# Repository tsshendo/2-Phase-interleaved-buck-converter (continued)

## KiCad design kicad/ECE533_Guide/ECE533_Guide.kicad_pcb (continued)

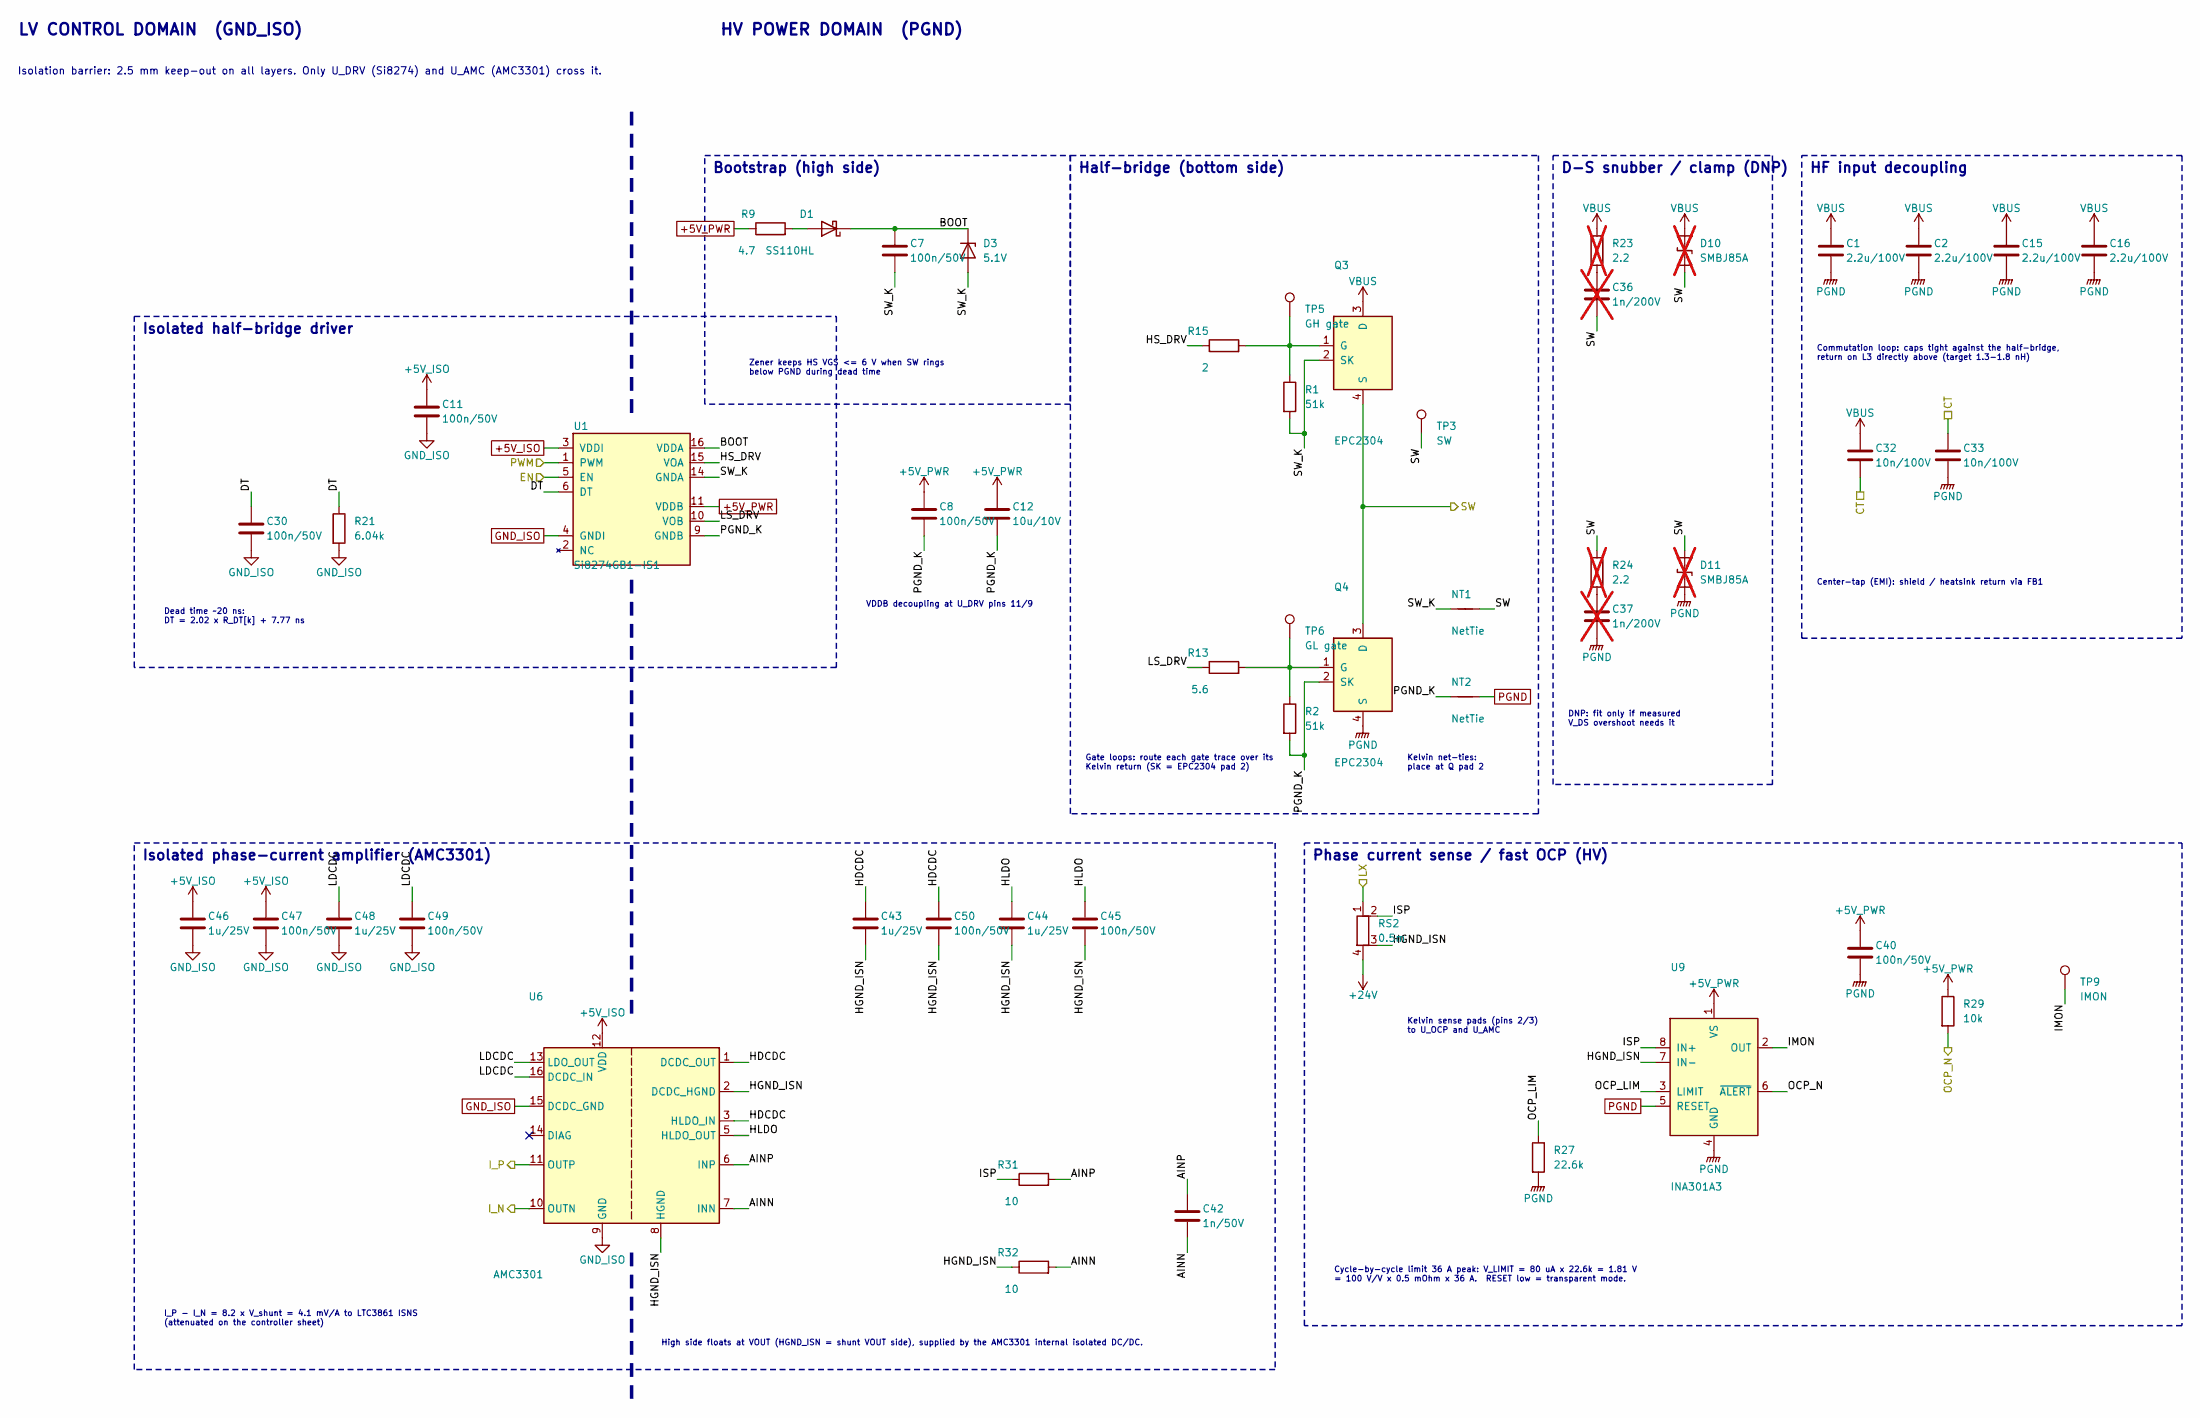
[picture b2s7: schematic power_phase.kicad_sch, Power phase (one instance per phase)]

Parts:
C1, C2, C15, C16: 2.2u/100V; C_0805_2012Metric; MPN GRM21BD72A225KE01L; LCSC C2981733
C7, C8, C11, C30, C40, C45, C47, C49, C50: 100n/50V; C_0603_1608Metric; MPN GRM188R71H104KA93D; LCSC C77055
C12: 10u/10V; C_0805_2012Metric; MPN GRM21BR71A106KE51L; LCSC C86038
C32, C33: 10n/100V; C_0603_1608Metric; MPN GRM188R72A103KA01D; LCSC C162275
C36, C37: 1n/200V; C_0805_2012Metric; MPN C0805C102J2GAC7800; LCSC C2170811; not fitted
C42: 1n/50V; C_0603_1608Metric; MPN GRM1885C1H102JA01D; LCSC C77026
C43, C44, C46, C48: 1u/25V; C_0603_1608Metric; MPN GRM188R71E105KA12D; LCSC C86020
D1: SS110HL; D_SOD-123F; MPN SS110HL-TP; LCSC C19996385
D3: 5.1V; D_SOD-123; MPN BZT52C5V1-TP; LCSC C78728
D10, D11: SMBJ85A; D_SMB; MPN SMBJ85A; not fitted
NT1, NT2: NetTie; NetTie-2_SMD_Pad0.5mm; MPN NetTie
Q3, Q4: EPC2304; EPC2304_QFN-7_3x5mm; MPN EPC2304; LCSC C6549215
R1, R2: 51k; R_0603_1608Metric; MPN RC0603FR-0751KL
R9: 4.7; R_0603_1608Metric; MPN RC0603FR-074R7L
R13: 5.6; R_0603_1608Metric; MPN RC0603FR-075R6L
R15: 2; R_0603_1608Metric; MPN RC0603FR-072RL
R21: 6.04k; R_0603_1608Metric; MPN RC0603FR-076K04L
R23, R24: 2.2; R_1206_3216Metric; MPN RC1206FR-072R2L; not fitted
R27: 22.6k; R_0603_1608Metric; MPN RC0603FR-0722K6L
R29: 10k; R_0603_1608Metric; MPN RC0603FR-0710KL
R31, R32: 10; R_0603_1608Metric; MPN RC0603FR-0710RL
RS2: 0.5m; R_2512_Kelvin; MPN CSS2H-2512R-L500F; LCSC C2073667
TP3: SW; TestPoint_Pad_D1.0mm; MPN Test pad (bare copper)
TP5: GH gate; TestPoint_Pad_D1.0mm; MPN Test pad (bare copper)
TP6: GL gate; TestPoint_Pad_D1.0mm; MPN Test pad (bare copper)
TP9: IMON; TestPoint_Pad_D1.0mm; MPN Test pad (bare copper)
U1: Si8274GB1-IS1; SOIC-16_3.9x9.9mm_P1.27mm; MPN Si8274GB1-IS1; LCSC C17368638
U6: AMC3301; SOIC-16W_7.5x10.3mm_P1.27mm; MPN AMC3301DWER; LCSC C2869778
U9: INA301A3; VSSOP-8_3x3mm_P0.65mm; MPN INA301A3IDGKR; LCSC C2861552

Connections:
+5V_ISO: C11.1, C46.1, C47.1, U1.3 (VDDI), U1.8 (VDDI), U6.12 (VDD); also elsewhere on the board
+5V_PWR: C8.1, C12.1, C40.1, R9.1, R29.1, U1.11 (VDDB), U9.1 (VS); also elsewhere on the board
+24V: RS2.4; also elsewhere on the board
/EN1: U1.5 (EN); also elsewhere on the board
/I1_N: U6.10 (OUTN); also elsewhere on the board
/I1_P: U6.11 (OUTP); also elsewhere on the board
/OCP1_N: R29.2, U9.6 (~ALERT); also elsewhere on the board
/PWM1: U1.1 (PWM); also elsewhere on the board
/Power stage (2 phases)/CT: C32.2, C33.1; also elsewhere on the board
/Power stage (2 phases)/LX1: RS2.1; also elsewhere on the board
/Power stage (2 phases)/Phase 1/AINN: C42.2, R32.2, U6.7 (INN)
/Power stage (2 phases)/Phase 1/AINP: C42.1, R31.2, U6.6 (INP)
/Power stage (2 phases)/Phase 1/BOOT: C7.1, D1.1 (K), D3.1 (K), U1.16 (VDDA)
/Power stage (2 phases)/Phase 1/DT: C30.1, R21.1, U1.6 (DT)
/Power stage (2 phases)/Phase 1/HDCDC: C43.1, C50.1, U6.1 (DCDC_OUT), U6.3 (HLDO_IN)
/Power stage (2 phases)/Phase 1/HGND_ISN: C43.2, C44.2, C45.2, C50.2, R32.1, RS2.3, U6.2 (DCDC_HGND), U6.8 (HGND), U9.7 (IN-)
/Power stage (2 phases)/Phase 1/HLDO: C44.1, C45.1, U6.5 (HLDO_OUT)
/Power stage (2 phases)/Phase 1/HS_DRV: R15.1, U1.15 (VOA)
/Power stage (2 phases)/Phase 1/IMON: TP9.1, U9.2 (OUT)
/Power stage (2 phases)/Phase 1/ISP: R31.1, RS2.2, U9.8 (IN+)
/Power stage (2 phases)/Phase 1/LDCDC: C48.1, C49.1, U6.13 (LDO_OUT), U6.16 (DCDC_IN)
/Power stage (2 phases)/Phase 1/LS_DRV: R13.1, U1.10 (VOB)
/Power stage (2 phases)/Phase 1/OCP_LIM: R27.1, U9.3 (LIMIT)
/Power stage (2 phases)/Phase 1/PGND_K: C8.2, C12.2, NT2.1, Q4.2 (SK), R2.2, U1.9 (GNDB)
/Power stage (2 phases)/Phase 1/SW_K: C7.2, D3.2 (A), NT1.1, Q3.2 (SK), R1.2, U1.14 (GNDA)
/Power stage (2 phases)/SW1: C36.2, D10.2 (A2), D11.1 (A1), NT1.2, Q3.4 (S), Q3.6 (S), Q4.3 (D), Q4.5 (D), Q4.7 (D), R24.1, TP3.1; also elsewhere on the board
GND_ISO: C11.2, C30.2, C46.2, C47.2, C48.2, C49.2, R21.2, U1.4 (GNDI), U6.9 (GND), U6.15 (DCDC_GND); also elsewhere on the board
unnamed: C36.1, R23.2
unnamed: C37.1, R24.2
unnamed: D1.2 (A), R9.2
unnamed: Q3.1 (G), R1.1, R15.2, TP5.1
unnamed: Q4.1 (G), R2.1, R13.2, TP6.1
PGND: C1.2, C2.2, C15.2, C16.2, C33.2, C37.2, C40.2, D11.2 (A2), NT2.2, Q4.4 (S), Q4.6 (S), R27.2, U9.4 (GND), U9.5 (RESET); also elsewhere on the board
VBUS: C1.1, C2.1, C15.1, C16.1, C32.1, D10.1 (A1), Q3.3 (D), Q3.5 (D), Q3.7 (D), R23.1; also elsewhere on the board

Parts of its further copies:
C3, C4, C17, C18: 2.2u/100V; C_0805_2012Metric; MPN GRM21BD72A225KE01L; LCSC C2981733
C9, C10, C13, C31, C41, C54, C56, C58, C59: 100n/50V; C_0603_1608Metric; MPN GRM188R71H104KA93D; LCSC C77055
C14: 10u/10V; C_0805_2012Metric; MPN GRM21BR71A106KE51L; LCSC C86038
C34, C35: 10n/100V; C_0603_1608Metric; MPN GRM188R72A103KA01D; LCSC C162275
C38, C39: 1n/200V; C_0805_2012Metric; MPN C0805C102J2GAC7800; LCSC C2170811; not fitted
C51: 1n/50V; C_0603_1608Metric; MPN GRM1885C1H102JA01D; LCSC C77026
C52, C53, C55, C57: 1u/25V; C_0603_1608Metric; MPN GRM188R71E105KA12D; LCSC C86020
D2: SS110HL; D_SOD-123F; MPN SS110HL-TP; LCSC C19996385
D4: 5.1V; D_SOD-123; MPN BZT52C5V1-TP; LCSC C78728
D12, D13: SMBJ85A; D_SMB; MPN SMBJ85A; not fitted
NT3, NT4: NetTie; NetTie-2_SMD_Pad0.5mm; MPN NetTie
Q5, Q6: EPC2304; EPC2304_QFN-7_3x5mm; MPN EPC2304; LCSC C6549215
R3, R4: 51k; R_0603_1608Metric; MPN RC0603FR-0751KL
R10: 4.7; R_0603_1608Metric; MPN RC0603FR-074R7L
R14: 5.6; R_0603_1608Metric; MPN RC0603FR-075R6L
R16: 2; R_0603_1608Metric; MPN RC0603FR-072RL
R22: 6.04k; R_0603_1608Metric; MPN RC0603FR-076K04L
R25, R26: 2.2; R_1206_3216Metric; MPN RC1206FR-072R2L; not fitted
R28: 22.6k; R_0603_1608Metric; MPN RC0603FR-0722K6L
R30: 10k; R_0603_1608Metric; MPN RC0603FR-0710KL
R33, R34: 10; R_0603_1608Metric; MPN RC0603FR-0710RL
RS3: 0.5m; R_2512_Kelvin; MPN CSS2H-2512R-L500F; LCSC C2073667
TP4: SW; TestPoint_Pad_D1.0mm; MPN Test pad (bare copper)
TP7: GH gate; TestPoint_Pad_D1.0mm; MPN Test pad (bare copper)
TP8: GL gate; TestPoint_Pad_D1.0mm; MPN Test pad (bare copper)
TP10: IMON; TestPoint_Pad_D1.0mm; MPN Test pad (bare copper)
U2: Si8274GB1-IS1; SOIC-16_3.9x9.9mm_P1.27mm; MPN Si8274GB1-IS1; LCSC C17368638
U7: AMC3301; SOIC-16W_7.5x10.3mm_P1.27mm; MPN AMC3301DWER; LCSC C2869778
U10: INA301A3; VSSOP-8_3x3mm_P0.65mm; MPN INA301A3IDGKR; LCSC C2861552

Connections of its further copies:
+5V_ISO: C13.1, C55.1, C56.1, U2.3 (VDDI), U2.8 (VDDI), U7.12 (VDD); also elsewhere on the board
+5V_PWR: C10.1, C14.1, C41.1, R10.1, R30.1, U2.11 (VDDB), U10.1 (VS); also elsewhere on the board
+24V: RS3.4; also elsewhere on the board
/EN2: U2.5 (EN); also elsewhere on the board
/I2_N: U7.10 (OUTN); also elsewhere on the board
/I2_P: U7.11 (OUTP); also elsewhere on the board
/OCP2_N: R30.2, U10.6 (~ALERT); also elsewhere on the board
/PWM2: U2.1 (PWM); also elsewhere on the board
/Power stage (2 phases)/CT: C34.2, C35.1; also elsewhere on the board
/Power stage (2 phases)/LX2: RS3.1; also elsewhere on the board
/Power stage (2 phases)/Phase 2/AINN: C51.2, R34.2, U7.7 (INN)
/Power stage (2 phases)/Phase 2/AINP: C51.1, R33.2, U7.6 (INP)
/Power stage (2 phases)/Phase 2/BOOT: C9.1, D2.1 (K), D4.1 (K), U2.16 (VDDA)
/Power stage (2 phases)/Phase 2/DT: C31.1, R22.1, U2.6 (DT)
/Power stage (2 phases)/Phase 2/HDCDC: C52.1, C59.1, U7.1 (DCDC_OUT), U7.3 (HLDO_IN)
/Power stage (2 phases)/Phase 2/HGND_ISN: C52.2, C53.2, C54.2, C59.2, R34.1, RS3.3, U7.2 (DCDC_HGND), U7.8 (HGND), U10.7 (IN-)
/Power stage (2 phases)/Phase 2/HLDO: C53.1, C54.1, U7.5 (HLDO_OUT)
/Power stage (2 phases)/Phase 2/HS_DRV: R16.1, U2.15 (VOA)
/Power stage (2 phases)/Phase 2/IMON: TP10.1, U10.2 (OUT)
/Power stage (2 phases)/Phase 2/ISP: R33.1, RS3.2, U10.8 (IN+)
/Power stage (2 phases)/Phase 2/LDCDC: C57.1, C58.1, U7.13 (LDO_OUT), U7.16 (DCDC_IN)
/Power stage (2 phases)/Phase 2/LS_DRV: R14.1, U2.10 (VOB)
/Power stage (2 phases)/Phase 2/OCP_LIM: R28.1, U10.3 (LIMIT)
/Power stage (2 phases)/Phase 2/PGND_K: C10.2, C14.2, NT4.1, Q6.2 (SK), R4.2, U2.9 (GNDB)
/Power stage (2 phases)/Phase 2/SW_K: C9.2, D4.2 (A), NT3.1, Q5.2 (SK), R3.2, U2.14 (GNDA)
/Power stage (2 phases)/SW2: C38.2, D12.2 (A2), D13.1 (A1), NT3.2, Q5.4 (S), Q5.6 (S), Q6.3 (D), Q6.5 (D), Q6.7 (D), R26.1, TP4.1; also elsewhere on the board
GND_ISO: C13.2, C31.2, C55.2, C56.2, C57.2, C58.2, R22.2, U2.4 (GNDI), U7.9 (GND), U7.15 (DCDC_GND); also elsewhere on the board
unnamed: C38.1, R25.2
unnamed: C39.1, R26.2
unnamed: D2.2 (A), R10.2
unnamed: Q5.1 (G), R3.1, R16.2, TP7.1
unnamed: Q6.1 (G), R4.1, R14.2, TP8.1
PGND: C3.2, C4.2, C17.2, C18.2, C35.2, C39.2, C41.2, D13.2 (A2), NT4.2, Q6.4 (S), Q6.6 (S), R28.2, U10.4 (GND), U10.5 (RESET); also elsewhere on the board
VBUS: C3.1, C4.1, C17.1, C18.1, C34.1, D12.1 (A1), Q5.3 (D), Q5.5 (D), Q5.7 (D), R25.1; also elsewhere on the board

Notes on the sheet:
LV CONTROL DOMAIN (GND_ISO)
HV POWER DOMAIN (PGND)
Isolation barrier: 2.5 mm keep-out on all layers. Only U_DRV (Si8274) and U_AMC (AMC3301) cross it.
Dead time ~20 ns: DT = 2.02 x R_DT[k] + 7.77 ns
Isolated half-bridge driver
Zener keeps HS VGS <= 6 V when SW rings below PGND during dead time
Bootstrap (high side)
VDDB decoupling at U_DRV pins 11/9
Gate loops: route each gate trace over its Kelvin return (SK = EPC2304 pad 2)
Kelvin net-ties: place at Q pad 2
Half-bridge (bottom side)
DNP: fit only if measured V_DS overshoot needs it
D-S snubber / clamp (DNP)
Commutation loop: caps tight against the half-bridge, return on L3 directly above (target 1.3-1.8 nH)
Center-tap (EMI): shield / heatsink return via FB1
HF input decoupling
Kelvin sense pads (pins 2/3) to U_OCP and U_AMC
Cycle-by-cycle limit 36 A peak: V_LIMIT = 80 uA x 22.6k = 1.81 V = 100 V/V x 0.5 mOhm x 36 A. RESET low = transparent mode.
Phase current sense / fast OCP (HV)
High side floats at VOUT (HGND_ISN = shunt VOUT side), supplied by the AMC3301 internal isolated DC/DC.
I_P - I_N = 8.2 x V_shunt = 4.1 mV/A to LTC3861 ISNS (attenuated on the controller sheet)
Isolated phase-current amplifier (AMC3301)

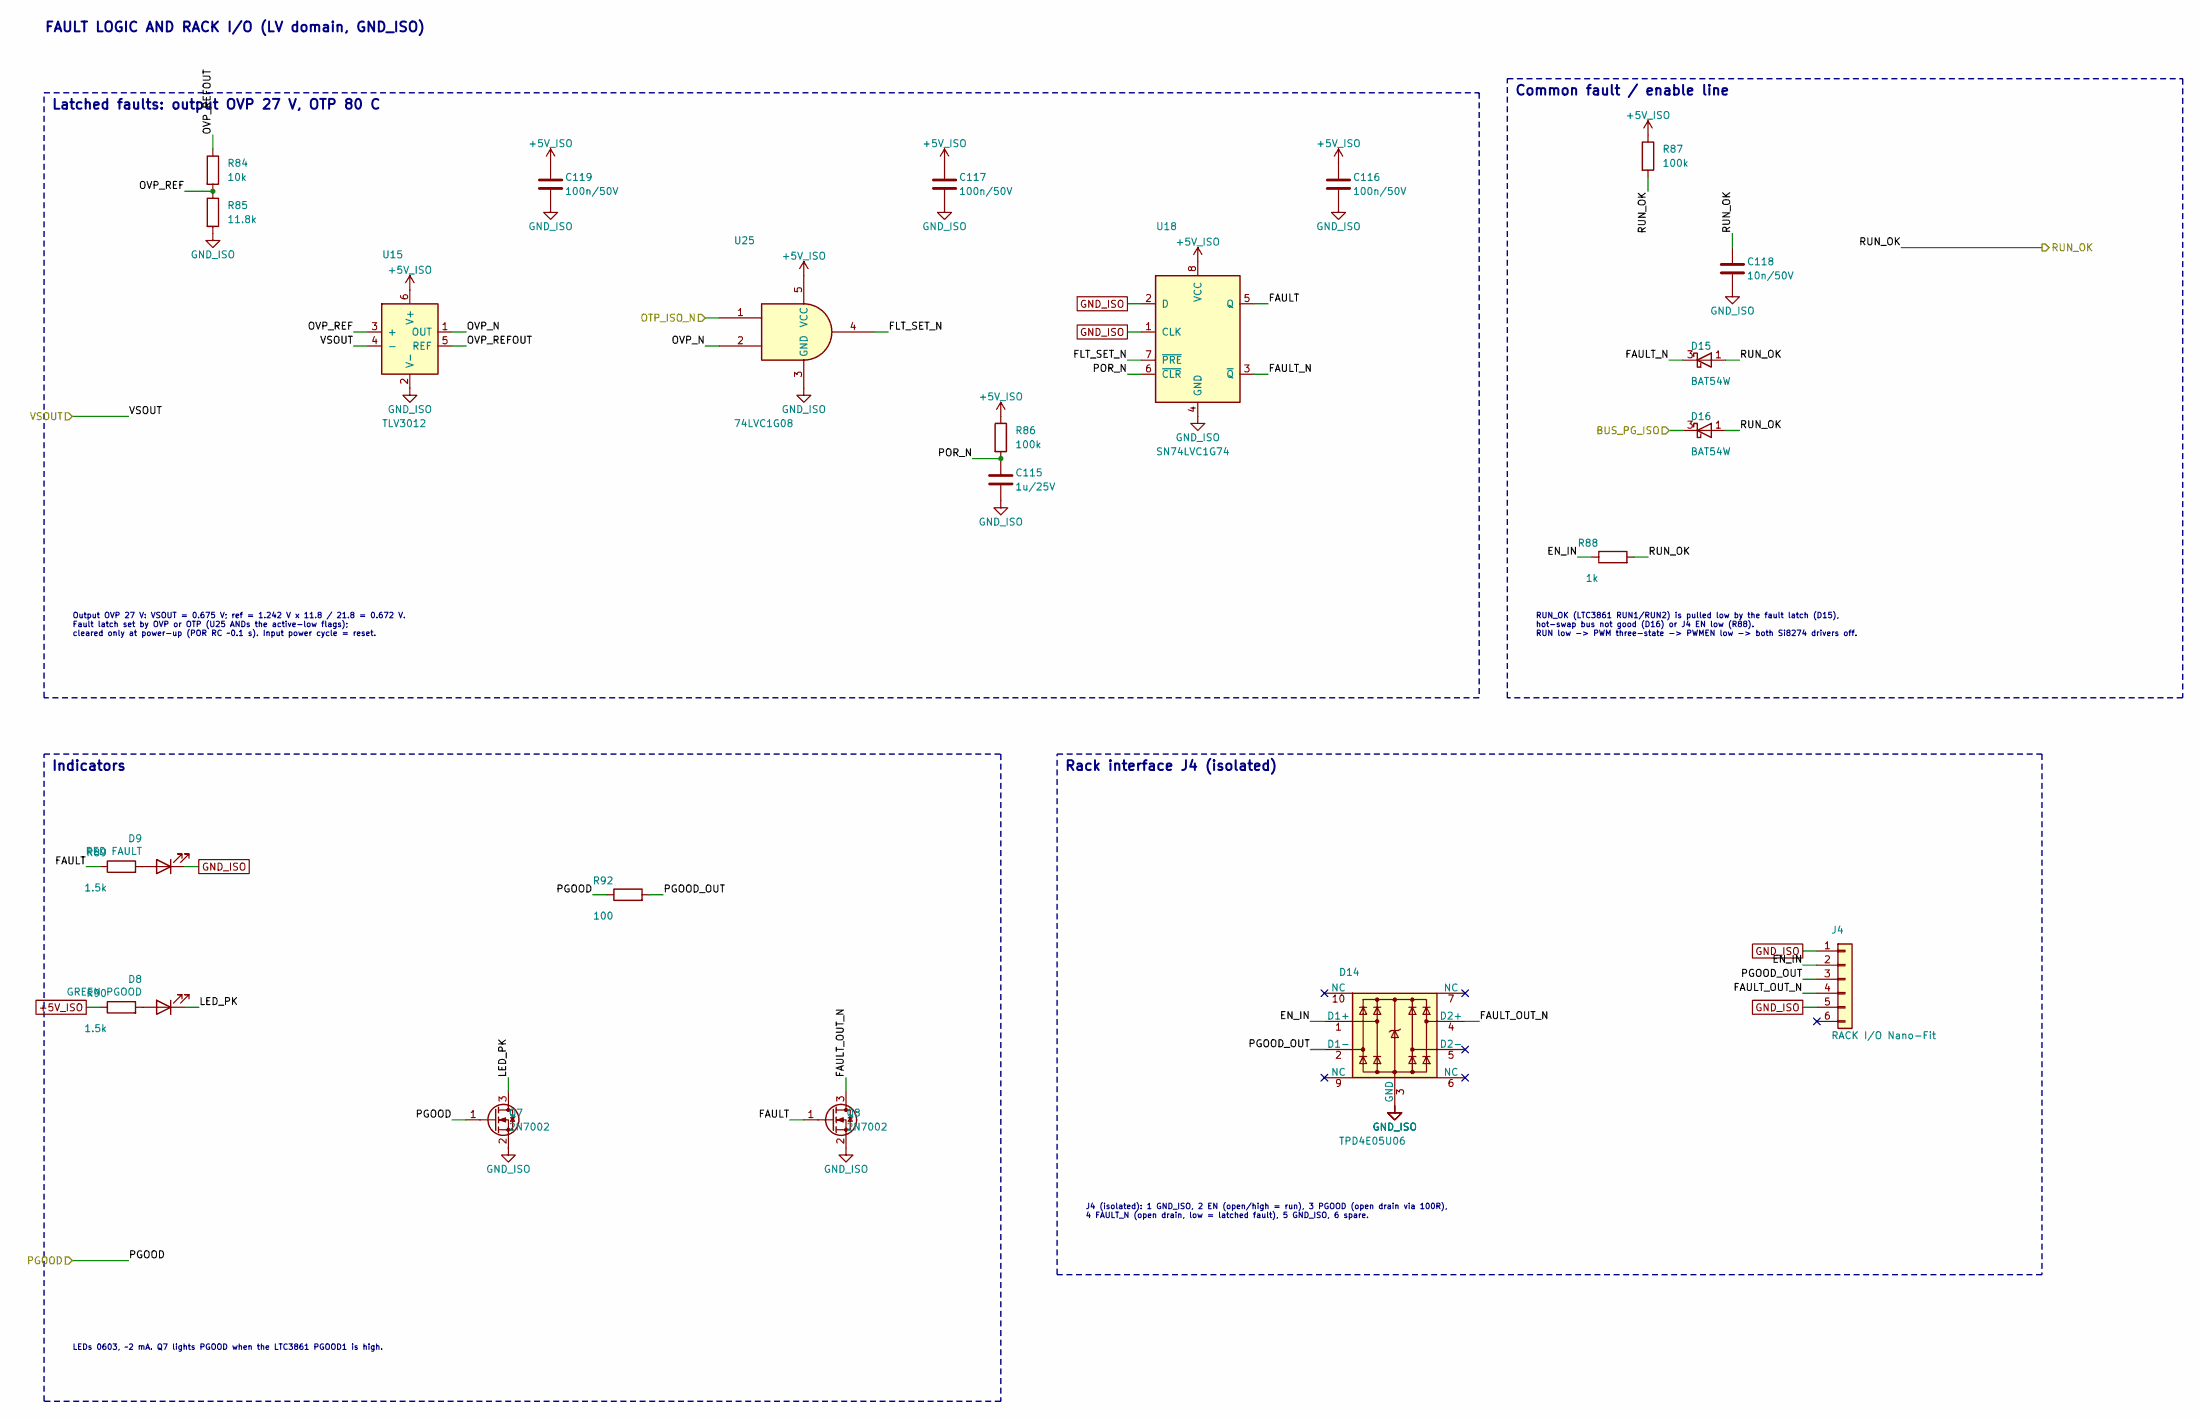
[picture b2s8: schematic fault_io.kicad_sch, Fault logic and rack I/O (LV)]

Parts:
C115: 1u/25V; C_0603_1608Metric; MPN GRM188R71E105KA12D; LCSC C86020
C116, C117, C119: 100n/50V; C_0603_1608Metric; MPN GRM188R71H104KA93D; LCSC C77055
C118: 10n/50V; C_0603_1608Metric; MPN GRM188R71H103KA01D; LCSC C77053
D8: GREEN PGOOD; LED_0603_1608Metric; MPN LTST-C191KGKT; LCSC C125098
D9: RED FAULT; LED_0603_1608Metric; MPN LTST-C191KRKT; LCSC C125099
D14: TPD4E05U06; USON-10_2.5x1.0mm_P0.5mm; MPN TPD4E05U06DQAR; LCSC C138714
D15, D16: BAT54W; SOT-323_SC-70; MPN BAT54W-7-F; LCSC C134417
J4: RACK I/O Nano-Fit; Molex_Nano-Fit_105313-xx06_1x06_P2.50mm_Horizontal; MPN 105313-1206; LCSC C17656275
Q7, Q8: 2N7002; SOT-23; MPN 2N7002LT1G; LCSC C16338
R84: 10k; R_0603_1608Metric; MPN RC0603FR-0710KL
R85: 11.8k; R_0603_1608Metric; MPN RC0603FR-0711K8L
R86, R87: 100k; R_0603_1608Metric; MPN RC0603FR-07100KL
R88: 1k; R_0603_1608Metric; MPN RC0603FR-071KL
R89, R90: 1.5k; R_0603_1608Metric; MPN RC0603FR-071K5L
R92: 100; R_0603_1608Metric; MPN RC0603FR-07100RL
U15: TLV3012; SOT-23-6; MPN TLV3012AIDBVR; LCSC C62505
U18: SN74LVC1G74; SSOP-8_2.95x2.8mm_P0.65mm; MPN SN74LVC1G74DCTR; LCSC C840104
U25: 74LVC1G08; SOT-23-5; MPN SN74LVC1G08DBVR; LCSC C7666

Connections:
+5V_ISO: C116.1, C117.1, C119.1, R86.1, R87.1, R90.1, U15.6 (V+), U18.8 (VCC), U25.5 (VCC); also elsewhere on the board
/BUS_PG_ISO: D16.3 (K); also elsewhere on the board
/Controller (LV)/Fault logic and rack I/O/EN_IN: D14.1 (D1+), J4.2, R88.1
/Controller (LV)/Fault logic and rack I/O/FAULT: Q8.1 (G), R89.1, U18.5 (Q)
/Controller (LV)/Fault logic and rack I/O/FAULT_N: D15.3 (K), U18.3 (~Q)
/Controller (LV)/Fault logic and rack I/O/FAULT_OUT_N: D14.4 (D2+), J4.4, Q8.3 (D)
/Controller (LV)/Fault logic and rack I/O/FLT_SET_N: U18.7 (~PRE), U25.4
/Controller (LV)/Fault logic and rack I/O/LED_PK: D8.1 (K), Q7.3 (D)
/Controller (LV)/Fault logic and rack I/O/OVP_N: U15.1 (OUT), U25.2
/Controller (LV)/Fault logic and rack I/O/OVP_REF: R84.2, R85.1, U15.3 (+)
/Controller (LV)/Fault logic and rack I/O/OVP_REFOUT: R84.1, U15.5 (REF)
/Controller (LV)/Fault logic and rack I/O/PGOOD_OUT: D14.2 (D1-), J4.3, R92.2
/Controller (LV)/Fault logic and rack I/O/POR_N: C115.1, R86.2, U18.6 (~CLR)
/Controller (LV)/PGOOD: Q7.1 (G), R92.1; also elsewhere on the board
/Controller (LV)/RUN_OK: C118.1, D15.1 (A), D16.1 (A), R87.2, R88.2; also elsewhere on the board
/Controller (LV)/VSOUT: U15.4 (-); also elsewhere on the board
/OTP_ISO_N: U25.1; also elsewhere on the board
GND_ISO: C115.2, C116.2, C117.2, C118.2, C119.2, D9.1 (K), D14.3 (GND), D14.8 (GND), J4.1, J4.5, Q7.2 (S), Q8.2 (S), R85.2, U15.2 (V-), U18.1 (CLK), U18.2 (D), U18.4 (GND), U25.3 (GND); also elsewhere on the board
unnamed: D8.2 (A), R90.2
unnamed: D9.2 (A), R89.2

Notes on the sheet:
FAULT LOGIC AND RACK I/O (LV domain, GND_ISO)
Output OVP 27 V: VSOUT = 0.675 V; ref = 1.242 V x 11.8 / 21.8 = 0.672 V. Fault latch set by OVP or OTP (U25 ANDs the active-low flags); cleared only at power-up (POR RC ~0.1 s). Input power cycle = reset.
Latched faults: output OVP 27 V, OTP 80 C
RUN_OK (LTC3861 RUN1/RUN2) is pulled low by the fault latch (D15), hot-swap bus not good (D16) or J4 EN low (R88). RUN low -> PWM three-state -> PWMEN low -> both Si8274 drivers off.
Common fault / enable line
LEDs 0603, ~2 mA. Q7 lights PGOOD when the LTC3861 PGOOD1 is high.
Indicators
J4 (isolated): 1 GND_ISO, 2 EN (open/high = run), 3 PGOOD (open drain via 100R), 4 FAULT_N (open drain, low = latched fault), 5 GND_ISO, 6 spare.
Rack interface J4 (isolated)

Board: 4 copper layers, 273 parts (134 on the bottom side), 140 nets, no tracks yet.

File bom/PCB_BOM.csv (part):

Item,Qty,Reference designators,Value,Manufacturer part number,Manufacturer,Digi-Key PN,Unit price (USD),Ext. price (USD),LCSC PN,Footprint,DNP,Notes
1,2,"AT1,AT2",SI86S620BC-IS,SI86S620BC-IS,Skyworks,863-SI86S620BC-IS-ND,3.28,,C7363570,SOIC-8_3.9x4.9mm_P1.27mm,,Required part (CLAUDE.md section 4)
2,10,"C1,C2,C3,C4,C15,C16,C17,C18,C74,C75",2.2u/100V,GRM21BD72A225KE01L,Murata,490-GRM21BD72A225KE01LCT-ND,0.44,,C2981733,C_0805_2012Metric,,Required part (CLAUDE.md section 4)
3,2,"C5,C6",110u/160V,EGXF161ELL111MK25S,Chemi-Con,565-EGXF161ELL111MK25S-ND,2.07,,C1598290,CP_Radial_D12.5mm_P5.00mm,,Required part (CLAUDE.md section 4)
4,39,"C7,C8,C9,C10,C11,C13,C30,C31,C40,C41,C45,C47,C49,C50,C54,C56,C58,C59,C68,C73,C80,C87,C88,C89,C90,C91,C94,C96,C98,C100,C102,C103,C111,C112,C113,C114,C116,C117,C119",100n/50V,GRM188R71H104KA93D,Murata,,,,C77055,C_0603_1608Metric,,
5,4,"C12,C14,C84,C86",10u/10V,GRM21BR71A106KE51L,Murata,,,,C86038,C_0805_2012Metric,,
6,4,"C32,C33,C34,C35",10n/100V,GRM188R72A103KA01D,Murata,,,,C162275,C_0603_1608Metric,,
7,4,"C42,C51,C105,C106",1n/50V,GRM1885C1H102JA01D,Murata,,,,C77026,C_0603_1608Metric,,
8,16,"C43,C44,C46,C48,C52,C53,C55,C57,C83,C85,C93,C95,C97,C99,C101,C115",1u/25V,GRM188R71E105KA12D,Murata,,,,C86020,C_0603_1608Metric,,
9,6,"C60,C61,C62,C63,C64,C65",10u/50V,GRM32ER71H106KA12L,Murata,,,,C77102,C_1210_3225Metric,,
10,2,"C66,C67",100u/35V,EEH-ZA1V101P,Panasonic,,,,,CP_Elec_8x10.5,,
11,2,"C70,C71",1u/100V,CC0805KKX7R0BB105,YAGEO,,,,C5370002,C_0805_2012Metric,,
12,1,C72,470n/25V,GRM188R71E474KA12D,Murata,,,,C77052,C_0603_1608Metric,,
13,1,C76,100n/100V,GRM188R72A104KA35D,Murata,,,,C77058,C_0603_1608Metric,,
14,2,"C77,C107",2.2n/50V,GRM188R71H222KA01D,Murata,,,,C86023,C_0603_1608Metric,,
15,2,"C78,C79",22u/10V,GRM31CR71A226KE15L,Murata,,,,C91604,C_1206_3216Metric,,
16,2,"C81,C108",4.7n/50V,GRM188R71H472KA01D,Murata,,,,C77057,C_0603_1608Metric,,
17,1,C82,47n/50V,GRM188R71H473KA61D,Murata,,,,C86027,C_0603_1608Metric,,
18,3,"C92,C104,C109",100p/50V,GRM1885C1H101JA01D,Murata,,,,C71664,C_0603_1608Metric,,
19,1,C118,10n/50V,GRM188R71H103KA01D,Murata,,,,C77053,C_0603_1608Metric,,
20,2,"D1,D2",SS110HL,SS110HL-TP,MCC,353-SS110HL-TPCT-ND,0.36,,C19996385,D_SOD-123F,,Required part (CLAUDE.md section 4)
21,2,"D3,D4",5.1V,BZT52C5V1-TP,MCC,,,,C78728,D_SOD-123,,
22,1,D5,30BQ100,VS-30BQ100TRPBF,Vishay,,,,,D_SMC,,
23,1,D6,SMDJ85CA,SMDJ85CA,Littelfuse,,,,C1978008,D_SMC,,
24,2,"D7,D14",TPD4E05U06,TPD4E05U06DQAR,TI,,,,C138714,USON-10_2.5x1.0mm_P0.5mm,,
25,1,D8,GREEN PGOOD,LTST-C191KGKT,Lite-On,,,,C125098,LED_0603_1608Metric,,
26,1,D9,RED FAULT,LTST-C191KRKT,Lite-On,,,,C125099,LED_0603_1608Metric,,
27,2,"D15,D16",BAT54W,BAT54W-7-F,Diodes Inc,,,,C134417,SOT-323_SC-70,,
28,1,FB1,600R@100MHz,BLM18KG601SN1D,Murata,,,,C85833,L_0603_1608Metric,,
29,1,J1,DC+ 72V,74650194R,Wurth Elektronik,,,,,Wurth_REDCUBE_74650194,,
30,1,J2,VOUT+,74650194R,Wurth Elektronik,,,,,Wurth_REDCUBE_74650194,,
31,1,J3,DC- return,74650194R,Wurth Elektronik,,,,,Wurth_REDCUBE_74650194,,
32,1,J4,RACK I/O Nano-Fit,105313-1206,Molex,WM14975-ND,2.54,,C17656275,Molex_Nano-Fit_105313-xx06_1x06_P2.50mm_Horizontal,,Required part (CLAUDE.md section 4)
33,1,J5,FAN Micro-Fit,43650-0400,Molex,,,,C277684,Molex_Micro-Fit_3.0_43650-0400_1x04_P3.00mm_Horizontal,,
34,1,J6,VOUT-,74650194R,Wurth Elektronik,,,,,Wurth_REDCUBE_74650194,,
35,1,L1,ERUC23-3R2K,ERUC23-3R2K,TDK,495-ERUC23-3R2KCT-ND,8.96,,,TDK_ERUC23,,"Required part (CLAUDE.md section 4); Custom footprint, drawn in Stage 3"
36,1,L2,33uH,XAL7070-333MEB,Coilcraft,,,,,L_Coilcraft_XAL7070-XXX,,
37,1,PS1,NME1S0505SC,NME1S0505SC,Murata,811-NME1S0505SC-ND,1.86,,C39128444,Murata_NME1S_SIP-4,,Required part (CLAUDE.md section 4)
38,2,"Q1,Q2",IPT015N10N5,IPT015N10N5,Infineon,,,,C108964,Infineon_PG-HSOF-8-1,,
39,4,"Q3,Q4,Q5,Q6",EPC2304,EPC2304,EPC,917-EPC2304CT-ND,9.05,,C6549215,EPC2304_QFN-7_3x5mm,,"Required part (CLAUDE.md section 4); Custom footprint, drawn in Stage 3"
40,2,"Q7,Q8",2N7002,2N7002LT1G,onsemi,,,,C16338,SOT-23,,
41,4,"R1,R2,R3,R4",51k,RC0603FR-0751KL,YAGEO,,,,,R_0603_1608Metric,,
42,2,"R9,R10",4.7,RC0603FR-074R7L,YAGEO,,,,,R_0603_1608Metric,,
43,2,"R13,R14",5.6,RC0603FR-075R6L,YAGEO,,,,,R_0603_1608Metric,,
44,2,"R15,R16",2,RC0603FR-072RL,YAGEO,,,,,R_0603_1608Metric,,
45,2,"R21,R22",6.04k,RC0603FR-076K04L,YAGEO,,,,,R_0603_1608Metric,,
46,2,"R27,R28",22.6k,RC0603FR-0722K6L,YAGEO,,,,,R_0603_1608Metric,,
47,15,"R29,R30,R48,R52,R53,R55,R58,R61,R62,R81,R84,R91,R93,R94,R95",10k,RC0603FR-0710KL,YAGEO,,,,,R_0603_1608Metric,,
48,5,"R31,R32,R33,R34,R44",10,RC0603FR-0710RL,YAGEO,,,,,R_0603_1608Metric,,
49,1,R40,5.49k,RC0603FR-075K49L,YAGEO,,,,,R_0603_1608Metric,,
50,1,R41,1M,RC0603FR-071ML,YAGEO,,,,,R_0603_1608Metric,,
51,1,R43,330,RC0603FR-07330RL,YAGEO,,,,,R_0603_1608Metric,,
52,1,R45,95.3k,RC1206FR-0795K3L,YAGEO,,,,,R_1206_3216Metric,,
53,1,R46,4.12k,RC0603FR-074K12L,YAGEO,,,,,R_0603_1608Metric,,
54,1,R47,13.0k,RC0603FR-0713KL,YAGEO,,,,,R_0603_1608Metric,,
55,1,R49,649k 0.1%,ERA-8AEB6493V,Panasonic,,,,,R_1206_3216Metric,,
56,4,"R50,R65,R69,R71",10.0k 0.1%,ERA-3AEB1002V,Panasonic,,,,,R_0603_1608Metric,,
57,1,R51,1.69M,RC0603FR-071M69L,YAGEO,,,,,R_0603_1608Metric,,
58,1,R54,200k,RC1206FR-07200KL,YAGEO,,,,,R_1206_3216Metric,,
59,1,R56,32.4k,RC0603FR-0732K4L,YAGEO,,,,,R_0603_1608Metric,,
60,1,R57,33.2k,RC0603FR-0733K2L,YAGEO,,,,,R_0603_1608Metric,,
61,3,"R59,R86,R87",100k,RC0603FR-07100KL,YAGEO,,,,,R_0603_1608Metric,,
62,1,R60,25.5k,RC0603FR-0725K5L,YAGEO,,,,,R_0603_1608Metric,,
63,1,R64,290k 0.1%,ERA-3AEB2903V,Panasonic,,,,,R_0603_1608Metric,,
64,1,R66,26.1k,RC0603FR-0726K1L,YAGEO,,,,,R_0603_1608Metric,,
65,2,"R67,R68",52.3k,RC0603FR-0752K3L,YAGEO,,,,,R_0603_1608Metric,,
66,2,"R70,R72",5.97k 0.1%,ERA-3AEB5971V,Panasonic,,,,,R_0603_1608Metric,,
67,4,"R73,R75,R77,R79",7.50k 0.1%,ERA-3AEB7501V,Panasonic,,,,,R_0603_1608Metric,,
68,4,"R74,R76,R78,R80",2.67k 0.1%,ERA-3AEB2671V,Panasonic,,,,,R_0603_1608Metric,,
69,2,"R82,R88",1k,RC0603FR-071KL,YAGEO,,,,,R_0603_1608Metric,,
70,1,R83,20k,RC0603FR-0720KL,YAGEO,,,,,R_0603_1608Metric,,
71,1,R85,11.8k,RC0603FR-0711K8L,YAGEO,,,,,R_0603_1608Metric,,
72,2,"R89,R90",1.5k,RC0603FR-071K5L,YAGEO,,,,,R_0603_1608Metric,,
73,1,R92,100,RC0603FR-07100RL,YAGEO,,,,,R_0603_1608Metric,,
74,1,R96,0R 100A,CSS2H-2512C-000,Bourns,,,,,R_2512_CSS2H,,"Custom footprint, drawn in Stage 3"
75,1,RS1,2m,CSS2H-2512R-2L00F,Bourns,,,,,R_2512_Kelvin,,"Custom footprint, drawn in Stage 3"
76,2,"RS2,RS3",0.5m,CSS2H-2512R-L500F,Bourns,,,,C2073667,R_2512_Kelvin,,"Custom footprint, drawn in Stage 3"
77,1,RT1,10k B3380,NCP18XH103F03RB,Murata,,,,C13564,R_0603_1608Metric,,
78,2,"U1,U2",Si8274GB1-IS1,Si8274GB1-IS1,Skyworks,,,,C17368638,SOIC-16_3.9x9.9mm_P1.27mm,,Required part (CLAUDE.md section 4)
79,1,U5,LTC3861IUHE#PBF,LTC3861IUHE#PBF,Analog Devices,,,,C686466,QFN-36-1EP_5x6mm_P0.5mm_EP3.6x4.1mm,,
80,2,"U6,U7",AMC3301,AMC3301DWER,TI,,,,C2869778,SOIC-16W_7.5x10.3mm_P1.27mm,,
81,1,U8,AMC3330,AMC3330DWER,TI,,,,C2999368,SOIC-16W_7.5x10.3mm_P1.27mm,,
82,2,"U9,U10",INA301A3,INA301A3IDGKR,TI,,,,C2861552,VSSOP-8_3x3mm_P0.65mm,,
83,1,U11,LM5012DDAR,LM5012DDAR,TI,,,,C6079494,HSOP-8-1EP_3.9x4.9mm_P1.27mm_EP2.41x3.1mm,,
84,1,U12,LM5069MM-2,LM5069MM-2/NOPB,TI,,,,,MSOP-10_3x3mm_P0.5mm,,
85,1,U13,VOM1271T,VOM1271T,Vishay,,,,C146286,SOP-4_3.8x4.1mm_P2.54mm,,
86,3,"U14,U15,U22",TLV3012,TLV3012AIDBVR,TI,,,,C62505,SOT-23-6,,
87,3,"U16,U17,U18",SN74LVC1G74,SN74LVC1G74DCTR,TI,,,,C840104,SSOP-8_2.95x2.8mm_P0.65mm,,
88,3,"U19,U20,U25",74LVC1G08,SN74LVC1G08DBVR,TI,,,,C7666,SOT-23-5,,
89,1,U21,TPS2553DBVR,TPS2553DBVR,TI,,,,C55266,SOT-23-6,,
90,4,"C36,C37,C38,C39",1n/200V,C0805C102J2GAC7800,KEMET,,,,C2170811,C_0805_2012Metric,DNP,DNP: footprint only
91,4,"D10,D11,D12,D13",SMBJ85A,SMBJ85A,Littelfuse,,,,,D_SMB,DNP,DNP: footprint only
92,1,F1,FUSE OPT,not fitted,,,,,,Fuse_Littelfuse_NANO2_456,DNP,"Custom footprint, drawn in Stage 3; DNP: footprint only"
93,4,"R23,R24,R25,R26",2.2,RC1206FR-072R2L,YAGEO,,,,,R_1206_3216Metric,DNP,DNP: footprint only
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
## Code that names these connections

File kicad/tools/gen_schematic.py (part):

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    sh.wire(dx_, dy_, xp, yp)
    sh.junction(g(42), yp)
    sh.wire(g(42), yp, g(42), yp - g(3))
    sh.hlabel('VIN_PROT', g(42), yp - g(3), 90, 'output')
    sh.flag(g(44), yp)
    sh.junction(g(44), yp)
    C(sh, 'C70', '1u', '100V', '0805', g(44), yp + g(1), None, '~PGND')
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    (cx, cy), _ = sh.parts[-1].pin_at('1')
    sh.flag(cx + g(2), cy - g(1))
    sh.wire(cx + g(2), cy - g(1), cx + g(4), cy - g(1))
    sh.label('HSC_VIN', cx + g(4), cy - g(1), 0)
    div(sh, 'R45', '95.3k', 'R46', '4.12k', g(44), g(46), 'VIN_PROT', 'UVLO', '~PGND', top_kw={'size': '1206'})
    C(sh, 'C72', '470n', '25V', '0603', g(78), g(54), 'TIMER', '~PGND')
    R(sh, 'R47', '13.0k', g(82), g(54), 'PWR', '~PGND')
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                  nets={'EN/UVLO': 'BUCK_EN', 'RON': 'BUCK_RON', 'BST': 'BUCK_BST', 'SW': 'BUCK_SW',
                        'FB': 'BUCK_FB', 'PGOOD': 'NC', 'GND': '~PGND'})
    (vx, vy), _ = buck.pin_at('VIN')
    sh.hlabel('VIN_PROT', g(12), vy, 180, 'input')
    sh.wire(g(12), vy, vx, vy)
    for i, (ref, val, volt, size) in enumerate((('C74', '2.2u', '100V', '0805'), ('C75', '2.2u', '100V', '0805'),
                                                ('C76', '100n', '100V', '0603'))):
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           nets={'D1+': 'FAN_5V', 'D1-': 'TACH', 'D2+': 'FAN_PWM', 'D2-': 'NC', '3': '~PGND', '8': '~PGND',
                 '6': 'NC', '7': 'NC', '9': 'NC', '10': 'NC'})
    sh.text('Limit 1.0 A typ (0.94-1.09 A): I_OS = 23950 / R_ILIM^0.977 (R in k).  Fan: 0.7 A start, 0.35 A run.\n'
            'PWM pin open = full speed (Sanyo 9GA); R63 DNP.   J5: 1 +5V, 2 GND, 3 TACH (open collector), 4 PWM.',
            g(10), g(90), size=1.0)
    sh.box(g(8), g(58), g(112), g(96), 'Fan output (separately current-limited)')

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def build_fault(sh):
    sh.text('FAULT LOGIC AND RACK I/O (LV domain, GND_ISO)', g(8), g(8), size=1.778, bold=True)
    yl = g(30)
    sh.hlabel('VSOUT', g(10), g(36), 180, 'input')
    sh.wire(g(10), g(36), g(14), g(36))
    sh.label('VSOUT', g(14), g(36), 0)
    sh.add('ECE533:TLV3012', 'U15', 'TLV3012', g(34), yl,
           fields={'MPN': 'TLV3012AIDBVR', 'Manufacturer': 'TI', 'LCSC': 'C62505'},
           nets={'+': 'OVP_REF', '-': 'VSOUT', 'REF': 'OVP_REFOUT', 'OUT': 'OVP_N',
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    bfp, bf = part('BAT54W-7-F', 'Diodes Inc', 'SOT323')
    R(sh, 'R87', '100k', g(122), g(16), '~+5V_ISO', 'RUN_OK')
    C(sh, 'C118', '10n', '50V', '0603', g(128), g(24), 'RUN_OK', '~GND_ISO')
    sh.hlabel('RUN_OK', g(150), g(24), 0, 'output')
    sh.wire(g(140), g(24), g(150), g(24))
    sh.label('RUN_OK', g(140), g(24), 180)
    for i, (ref, k) in enumerate((('D15', 'FAULT_N'), ('D16', '>BUS_PG_ISO:input'))):
        d = sh.add('Diode:BAT54W', ref, 'BAT54W', g(126), g(32 + 5 * i), footprint=bfp, fields=dict(bf))
        d.x, d.y = g(126), g(32 + 5 * i)
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    nfp, nf = part('2N7002LT1G', 'onsemi', 'SOT23')
    sh.add('Transistor_FET:2N7002', 'Q7', '2N7002', g(40), g(86), footprint=nfp, fields=dict(nf),
           nets={'G': 'PGOOD', 'S': '~GND_ISO', 'D': 'LED_PK'})
    sh.hlabel('PGOOD', g(10), g(96), 180, 'input')
    sh.wire(g(10), g(96), g(14), g(96))
    sh.label('PGOOD', g(14), g(96), 0)
    sh.add('Transistor_FET:2N7002', 'Q8', '2N7002', g(64), g(86), footprint=nfp, fields=dict(nf),
           nets={'G': 'FAULT', 'S': '~GND_ISO', 'D': 'FAULT_OUT_N'})
    R(sh, 'R92', '100', g(48), g(70), 'PGOOD', 'PGOOD_OUT', horiz=True)
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        return (x, y)

    # input protection -> aux supply
    a, b = pin(s_in, 'VIN_PROT'), pin(s_aux, 'VIN_PROT')
    route(sh, a, b, a[0] + g(3))
    sh.label('VIN_PROT', a[0] + g(1), a[1], 0)
    # controller <-> power stage: one lane per signal, lanes step right
    for i, n in enumerate([x for x in ps_l if x]):
        route(sh, pin(s_ctl, n), pin(s_ps, n), g(46 + 2 * i))
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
